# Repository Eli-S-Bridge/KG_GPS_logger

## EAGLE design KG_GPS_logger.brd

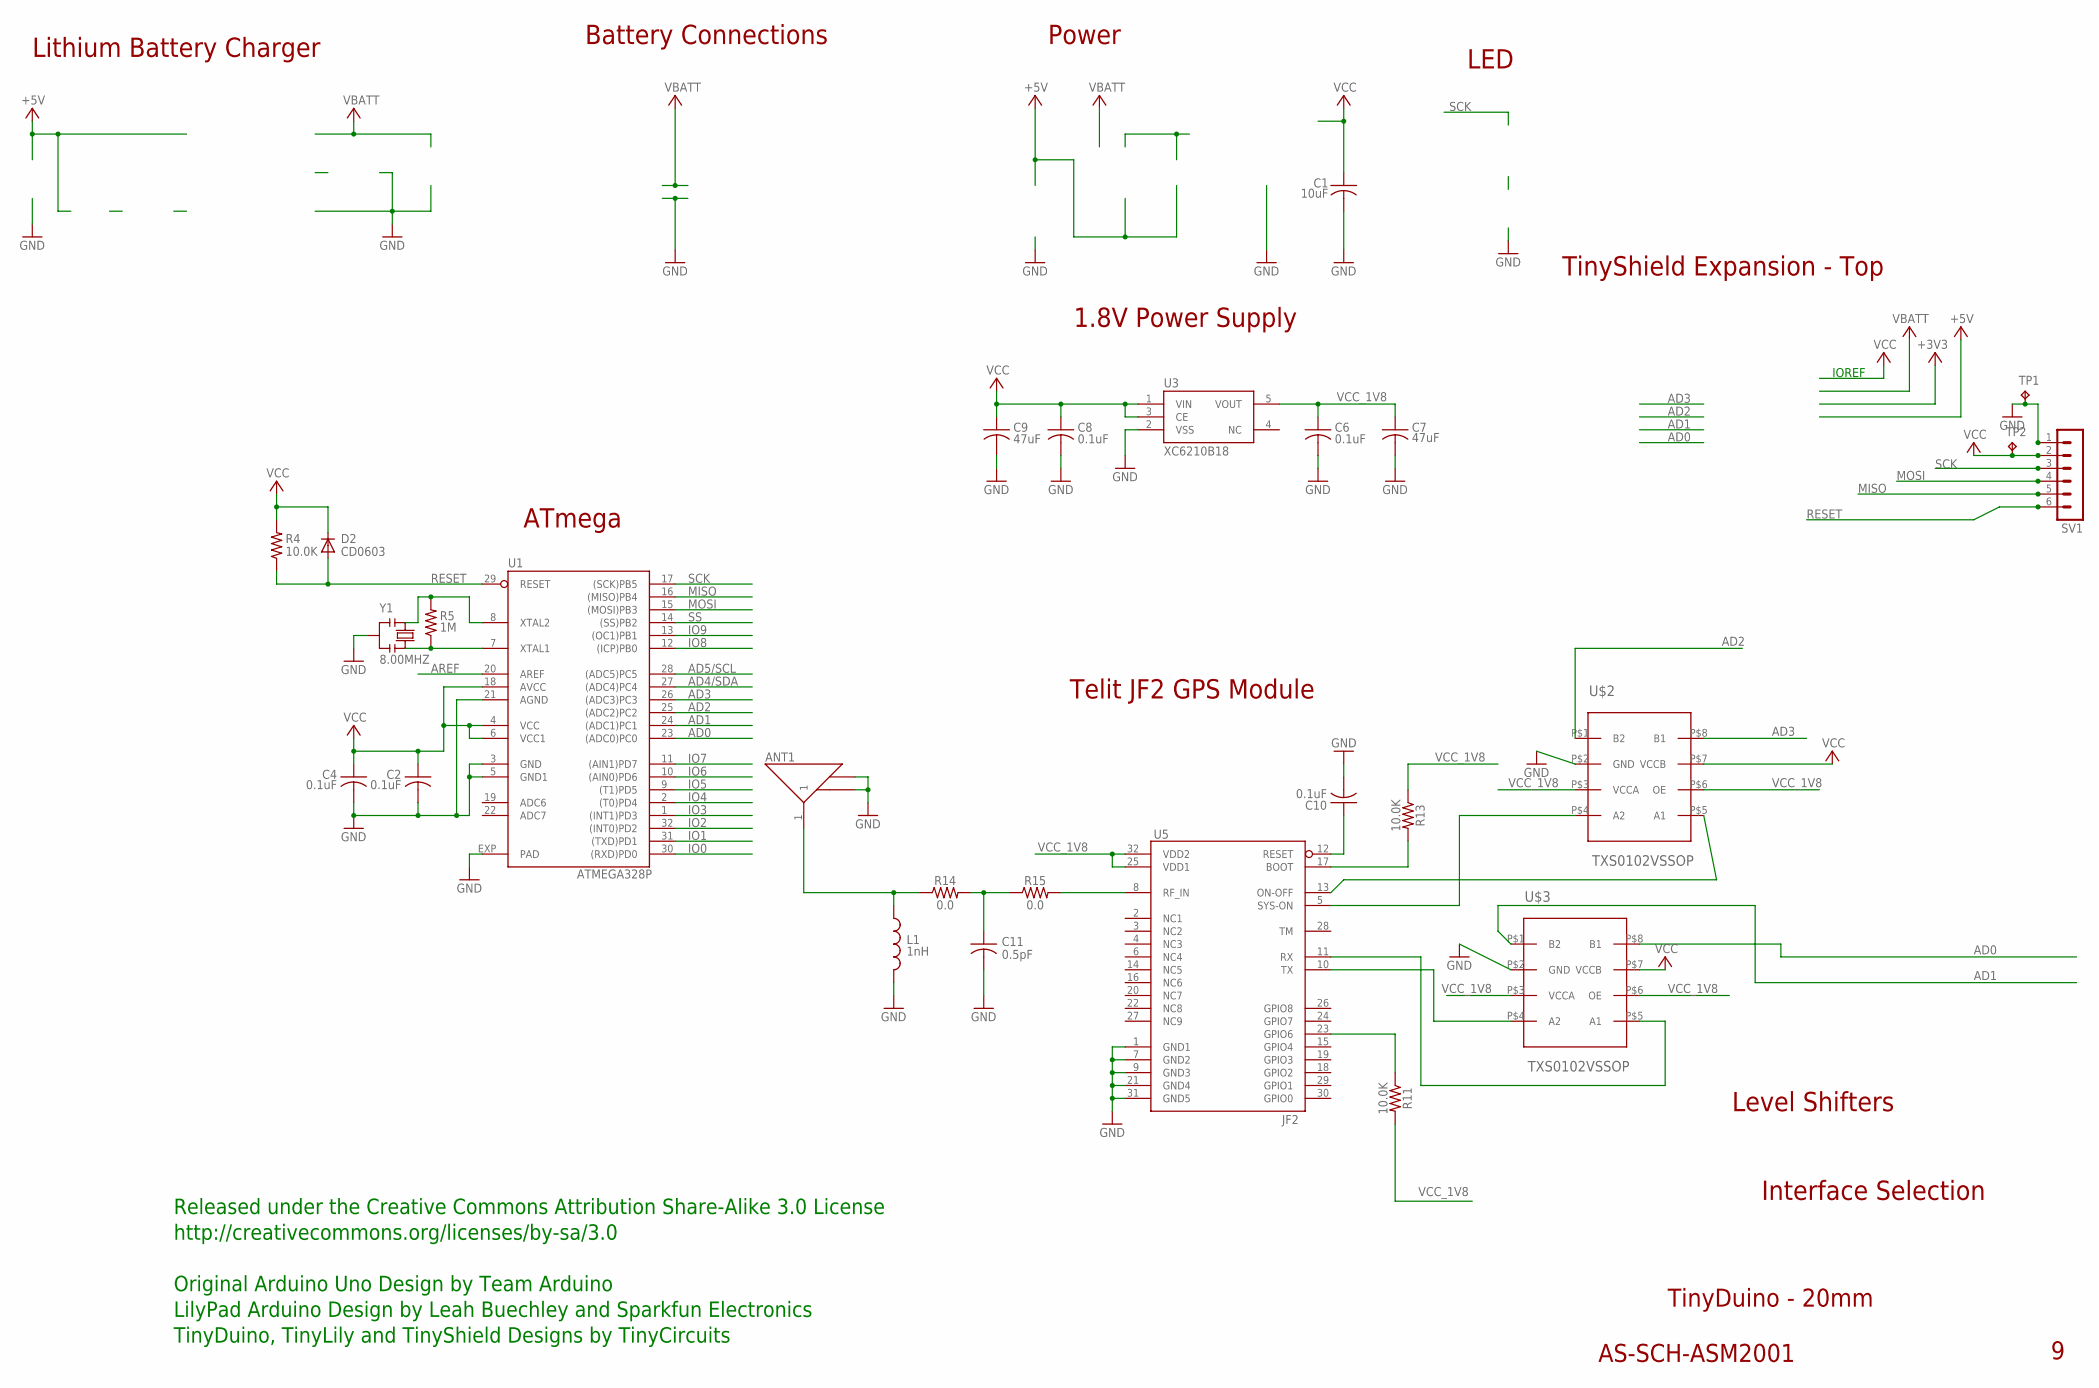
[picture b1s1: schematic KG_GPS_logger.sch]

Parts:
ANT1: AS-ITM-00109; W3011
C1: 10uF; C0603; PARTNO AS-ITM-00002
C2, C4, C6, C8, C10: 0.1uF; C0402; PARTNO AS-ITM-00008
C7: 47uF; C1206
C9: 47uF; C1206; PARTNUM AS-ITM-00049
C11: 0.5pF; C0402
D2: CD0603; 0603; PARTNO AS-ITM-00009
L1: 1nH; 0402
R4, R13: 10.0K; 0402; PARTNO AS-ITM-00032
R5: 1M; 0402@1; PARTNO AS-ITM-00005
R11: 10.0K; 0402
R14, R15: 0.0; 0402
SV1: MA06-1
TP1, TP2: TPTP17SQ; TP17SQ
U1: ATMEGA328P; ATMEL_QFN32; PARTNO AS-ITM-00013
U3: XC6210B18; SOT-25; PARTNO AS-ITM-00075
U5: JF2
U$2, U$3: TXS0102VSSOP; VSSOP_3MM
Y1: 8.00MHZ; RESONATOR_SMALL; PARTNO AS-ITM-00027

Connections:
AD0: U1.23 ((ADC0)PC0), U$3.P$8 (B1)
AD1: U1.24 ((ADC1)PC1), U$3.P$1 (B2)
AD2: U1.25 ((ADC2)PC2), U$2.P$1 (B2)
AD3: U1.26 ((ADC3)PC3), U$2.P$8 (B1)
AD4/SDA: U1.27 ((ADC4)PC4)
AD5/SCL: U1.28 ((ADC5)PC5)
AREF: U1.20 (AREF)
GND: ANT1.2 (G1), ANT1.3 (G2), C1.2, C2.2, C4.2, C6.2, C7.2, C8.2, C9.2, C10.2, C11.2, L1.2, SV1.1, TP1.TP, U1.3 (GND), U1.5 (GND1), U1.21 (AGND), U1.EXP (PAD), U3.2 (VSS), U5.1 (GND1), U5.7 (GND2), U5.9 (GND3), U5.21 (GND4), U5.31 (GND5), U$2.P$2 (GND), U$3.P$2 (GND), Y1.2
IO0: U1.30 ((RXD)PD0)
IO1: U1.31 ((TXD)PD1)
IO2: U1.32 ((INT0)PD2)
IO3: U1.1 ((INT1)PD3)
IO4: U1.2 ((T0)PD4)
IO5: U1.9 ((T1)PD5)
IO6: U1.10 ((AIN0)PD6)
IO7: U1.11 ((AIN1)PD7)
IO8: U1.12 ((ICP)PB0)
IO9: U1.13 ((OC1)PB1)
MISO: SV1.5, U1.16 ((MISO)PB4)
MOSI: SV1.4, U1.15 ((MOSI)PB3)
unnamed: R5.2, U1.8 (XTAL2), Y1.1
unnamed: R5.1, U1.7 (XTAL1), Y1.3
unnamed: R11.1, U5.23 (GPIO6)
unnamed: ANT1.1, L1.1, R14.1
unnamed: R13.2, U5.17 (BOOT)
unnamed: U5.13 (ON-OFF), U$2.P$5 (A1)
unnamed: U5.5 (SYS-ON), U$2.P$4 (A2)
unnamed: U5.11 (RX), U$3.P$5 (A1)
unnamed: U5.10 (TX), U$3.P$4 (A2)
unnamed: C10.1, U5.12 (RESET)
unnamed: C11.1, R14.2, R15.1
unnamed: R15.2, U5.8 (RF_IN)
RESET: D2.A, R4.1, SV1.6, U1.29 (RESET)
SCK: SV1.3, U1.17 ((SCK)PB5)
SS: U1.14 ((SS)PB2)
VCC: C1.1, C2.1, C4.1, C8.1, C9.1, D2.C, R4.2, SV1.2, TP2.TP, U1.4 (VCC), U1.6 (VCC1), U1.18 (AVCC), U3.1 (VIN), U3.3 (CE), U$2.P$7 (VCCB), U$3.P$7 (VCCB)
VCC_1V8: C6.1, C7.1, R11.2, R13.1, U3.5 (VOUT), U5.25 (VDD1), U5.32 (VDD2), U$2.P$3 (VCCA), U$2.P$6 (OE), U$3.P$3 (VCCA), U$3.P$6 (OE)

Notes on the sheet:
IOREF
TinyShield Expansion - Top
ATmega
Power
LED
TinyDuino - 20mm
AS-SCH-ASM2001
Released under the Creative Commons Attribution Share-Alike 3.0 License
http://creativecommons.org/licenses/by-sa/3.0
Original Arduino Uno Design by Team Arduino
TinyDuino, TinyLily and TinyShield Designs by TinyCircuits
LilyPad Arduino Design by Leah Buechley and Sparkfun Electronics
Lithium Battery Charger
Battery Connections
1.8V Power Supply
Telit JF2 GPS Module
Level Shifters
Interface Selection

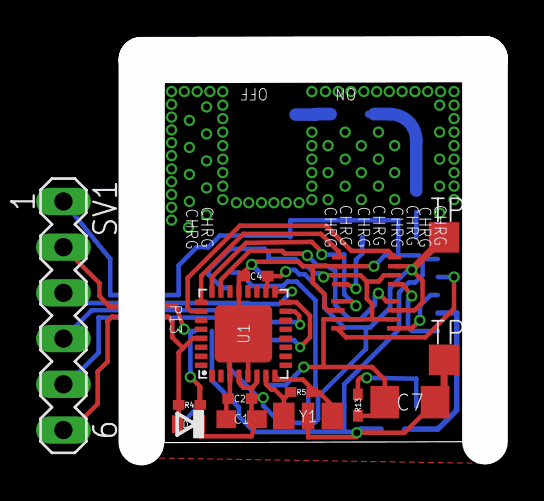
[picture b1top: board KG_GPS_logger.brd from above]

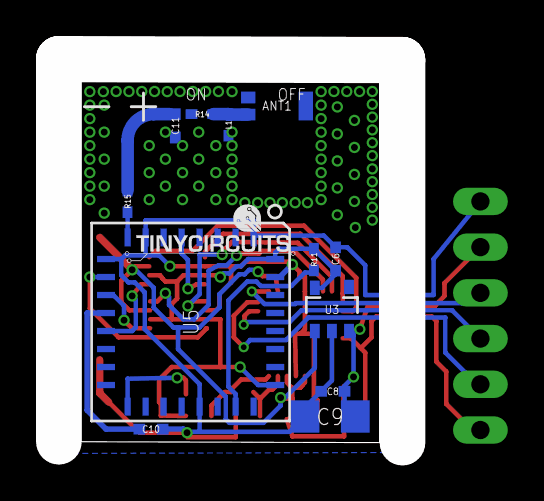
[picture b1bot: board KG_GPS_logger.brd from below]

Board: 2 copper layers, 16.6 x 20.1 mm, 28 parts (12 on the bottom side), 23 nets.

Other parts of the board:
U$1: DOCFIELD-TINYCIRCUITS-PCB

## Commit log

2017-03-29 new repo start
